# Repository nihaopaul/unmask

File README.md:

# unmask

Unmask was created by Paul Adams and Simone Rebaudengo in shanghai. 
The original idea was inspired by sharing emotions while 
wearing a mask, the first design was based on littleHeart bits 
by Mika Lin and Edward Jiang from Xinchejian

# Board Design
The latest Design has yet to be tested, its redesigned from the bottom up.
While still using an AVR microcontroller but this time using a ATTINY85 instead of a mega8 which the Littleheart bits was based on.

# Code
Unfortunatly we have not yet written code for the latest hardware, but the original code is published here as a placeholder.

# next steps

Build out one fully functional mask

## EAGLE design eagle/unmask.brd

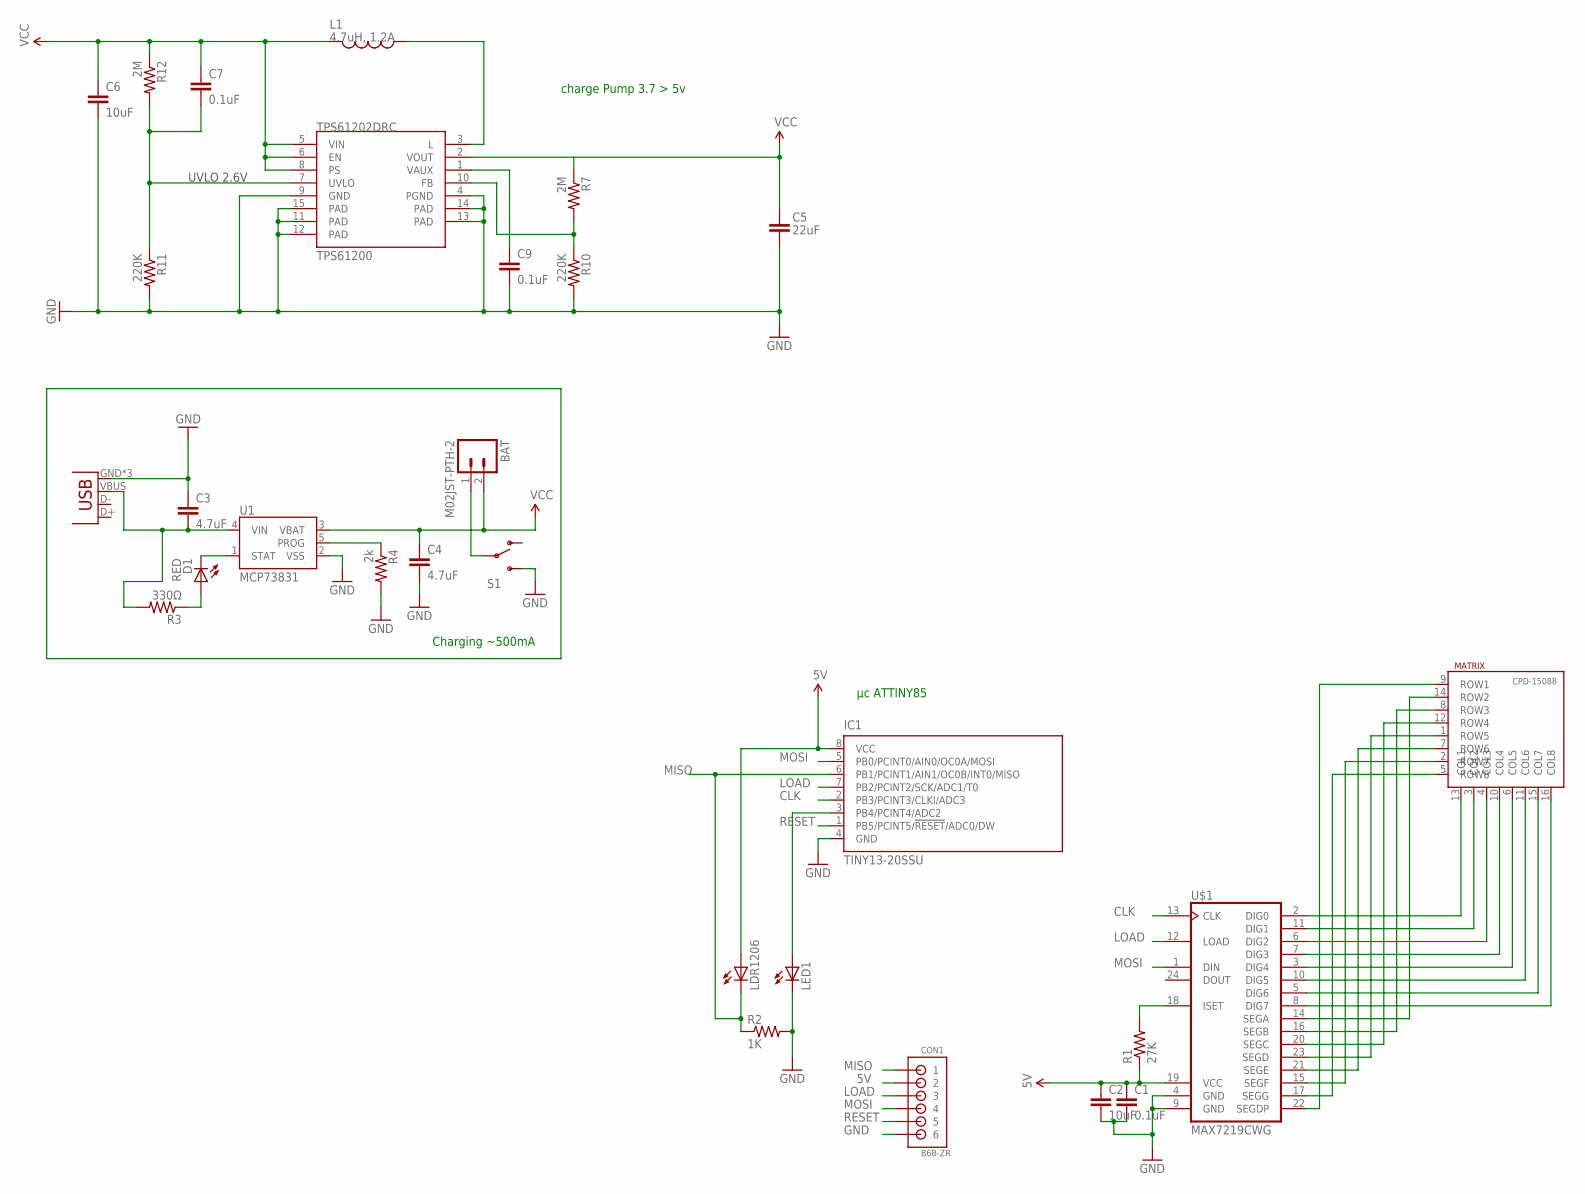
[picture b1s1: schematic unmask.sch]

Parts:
BAT: M02JST-PTH-2; JST-2-PTH
C1, C7, C9: 0.1uF; 0805
C2, C6: 10uF; 0805
C3, C4: 4.7uF; 0805
C5: 22uF; 0805
CON1: B6B-ZR
D1: RED; LED-1206
IC1: TINY13-20SSU; 8S1
JP2: USB-MICROB
L1: 4.7uH, 1.2A; CDRH2D09
LDR1206: LED_E; LED_1206
LED1: LED_E; LED_1206
MATRIX: CPD-15088YGD2/A; CPD15088
R1: 27K; 0805
R2: 1K; 0603-RES
R3: 330Ω; 0805
R4: 2k; 0805
R7, R12: 2M; 0805
R10, R11: 220K; 0805
S1: SWITCH-SPDTSMD2; SWITCH-SPDT-SMD
TPS61202DRC: TPS61200; QFN-10_PAD
U1: MCP73831; SOT23-5
U$1: MAX7219CWG; SO24L

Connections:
5V: C1.1, C2.1, C5.1, CON1.2, IC1.8 (VCC), LDR1206.A, R1.1, R7.1, R7.2, R10.1, TPS61202DRC.2 (VOUT), TPS61202DRC.10 (FB), U$1.19 (VCC)
CLK: IC1.2 (PB3/PCINT3/CLKI/ADC3), U$1.13 (CLK)
GND: C1.2, C2.2, C3.1, C4.2, C5.2, C6.2, C9.2, CON1.6, IC1.4 (GND), JP2.GND, JP2.MT1 (GND), JP2.MT2 (GND), R4.2, R10.2, R11.2, S1.3 (S), TPS61202DRC.4 (PGND), TPS61202DRC.9 (GND), TPS61202DRC.11 (PAD), TPS61202DRC.12 (PAD), TPS61202DRC.13 (PAD), TPS61202DRC.14 (PAD), TPS61202DRC.15 (PAD), U1.2 (VSS), U$1.4 (GND), U$1.9 (GND)
LOAD: CON1.3, IC1.7 (PB2/PCINT2/SCK/ADC1/T0), U$1.12 (LOAD)
MISO: CON1.1, IC1.6 (PB1/PCINT1/AIN1/OC0B/INT0/MISO), LDR1206.C, R2.1
MOSI: CON1.4, IC1.5 (PB0/PCINT0/AIN0/OC0A/MOSI), U$1.1 (DIN)
unnamed: MATRIX.2 (ROW7), U$1.15 (SEGF)
unnamed: MATRIX.13 (COL1), U$1.2 (DIG0)
unnamed: MATRIX.3 (COL2), U$1.11 (DIG1)
unnamed: MATRIX.4 (COL3), U$1.6 (DIG2)
unnamed: MATRIX.10 (COL4), U$1.7 (DIG3)
unnamed: MATRIX.6 (COL5), U$1.3 (DIG4)
unnamed: MATRIX.11 (COL6), U$1.10 (DIG5)
unnamed: MATRIX.15 (COL7), U$1.5 (DIG6)
unnamed: MATRIX.16 (COL8), U$1.8 (DIG7)
unnamed: MATRIX.9 (ROW1), U$1.22 (SEGDP)
unnamed: MATRIX.5 (ROW8), U$1.17 (SEGG)
unnamed: MATRIX.7 (ROW6), U$1.21 (SEGE)
unnamed: MATRIX.1 (ROW5), U$1.23 (SEGD)
unnamed: MATRIX.12 (ROW4), U$1.20 (SEGC)
unnamed: MATRIX.8 (ROW3), U$1.16 (SEGB)
unnamed: MATRIX.14 (ROW2), U$1.14 (SEGA)
unnamed: LED1.C, R2.2
unnamed: R1.2, U$1.18 (ISET)
unnamed: IC1.3 (PB4/PCINT4/ADC2), LED1.A
unnamed: C3.2, JP2.VBUS, R3.2, U1.4 (VIN)
unnamed: D1.C, U1.1 (STAT)
unnamed: D1.A, R3.1
unnamed: L1.P$1 (1), TPS61202DRC.3 (L)
unnamed: C9.1, TPS61202DRC.1 (VAUX)
unnamed: R4.1, U1.5 (PROG)
unnamed: BAT.1, S1.2
RESET: CON1.5, IC1.1 (PB5/PCINT5/!RESET!/ADC0/DW)
UVLO: C7.2, R11.1, R12.2, TPS61202DRC.7 (UVLO)
VIN: BAT.2, C4.1, C6.1, C7.1, L1.P$2 (2), R12.1, TPS61202DRC.5 (VIN), TPS61202DRC.6 (EN), TPS61202DRC.8 (PS), U1.3 (VBAT)

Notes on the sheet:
Charging ~500mA
UVLO 2.6V
charge Pump 3.7 > 5v
µc ATTINY85

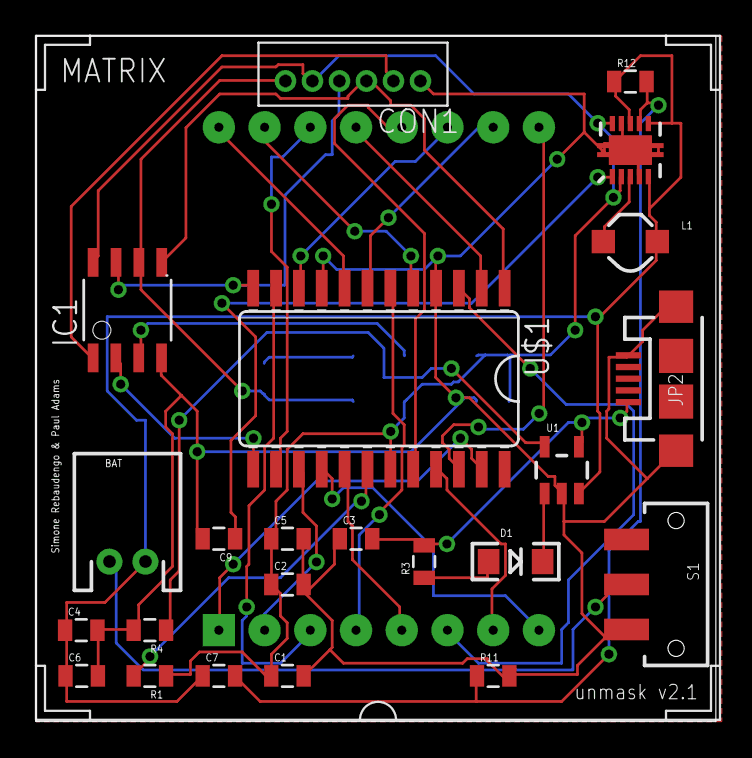
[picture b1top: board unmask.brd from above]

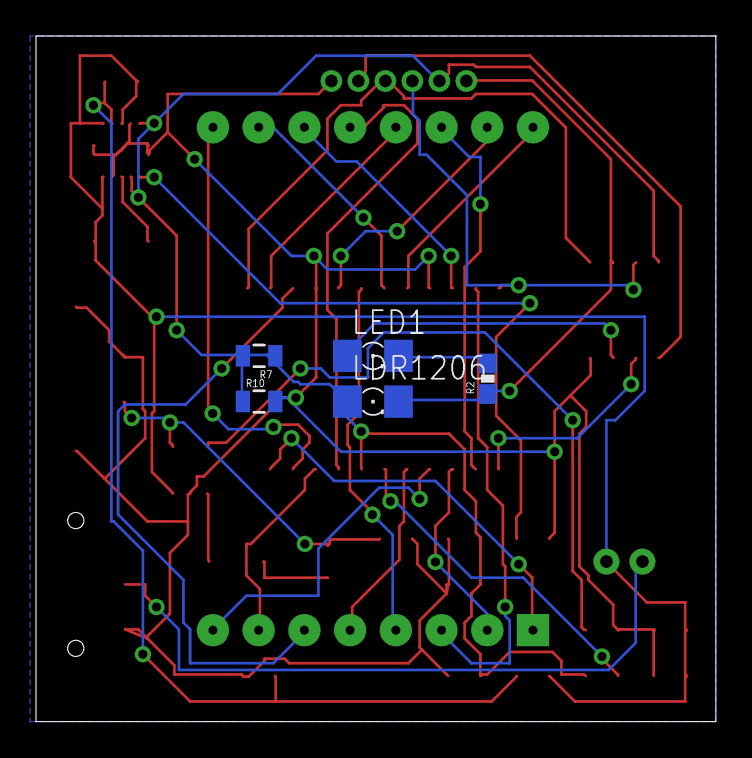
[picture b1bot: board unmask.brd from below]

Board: 2 copper layers, 37.8 x 38.1 mm, 29 parts (5 on the bottom side), 35 nets.

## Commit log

2015-04-23 first checkin of unmasked, added eagle files and original arduino code

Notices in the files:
parts and their libraries:
SparkFun-Connectors: Licensing: Creative Commons ShareAlike 4.0 International - https://creativecommons.org/licenses/by-sa/4.0
